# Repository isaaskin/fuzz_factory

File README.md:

# fuzz_factory
Fuzz Factory Guitar Effect Pedal

Schematic and layout drawing on Eagle Cad Software.
Ready to print. 
Potentiometer, LED, DC jack input, Battery input, 3.5mm mono input-output jack and 3DPT switch connections are ready on the board.
Minimalistic cable design.

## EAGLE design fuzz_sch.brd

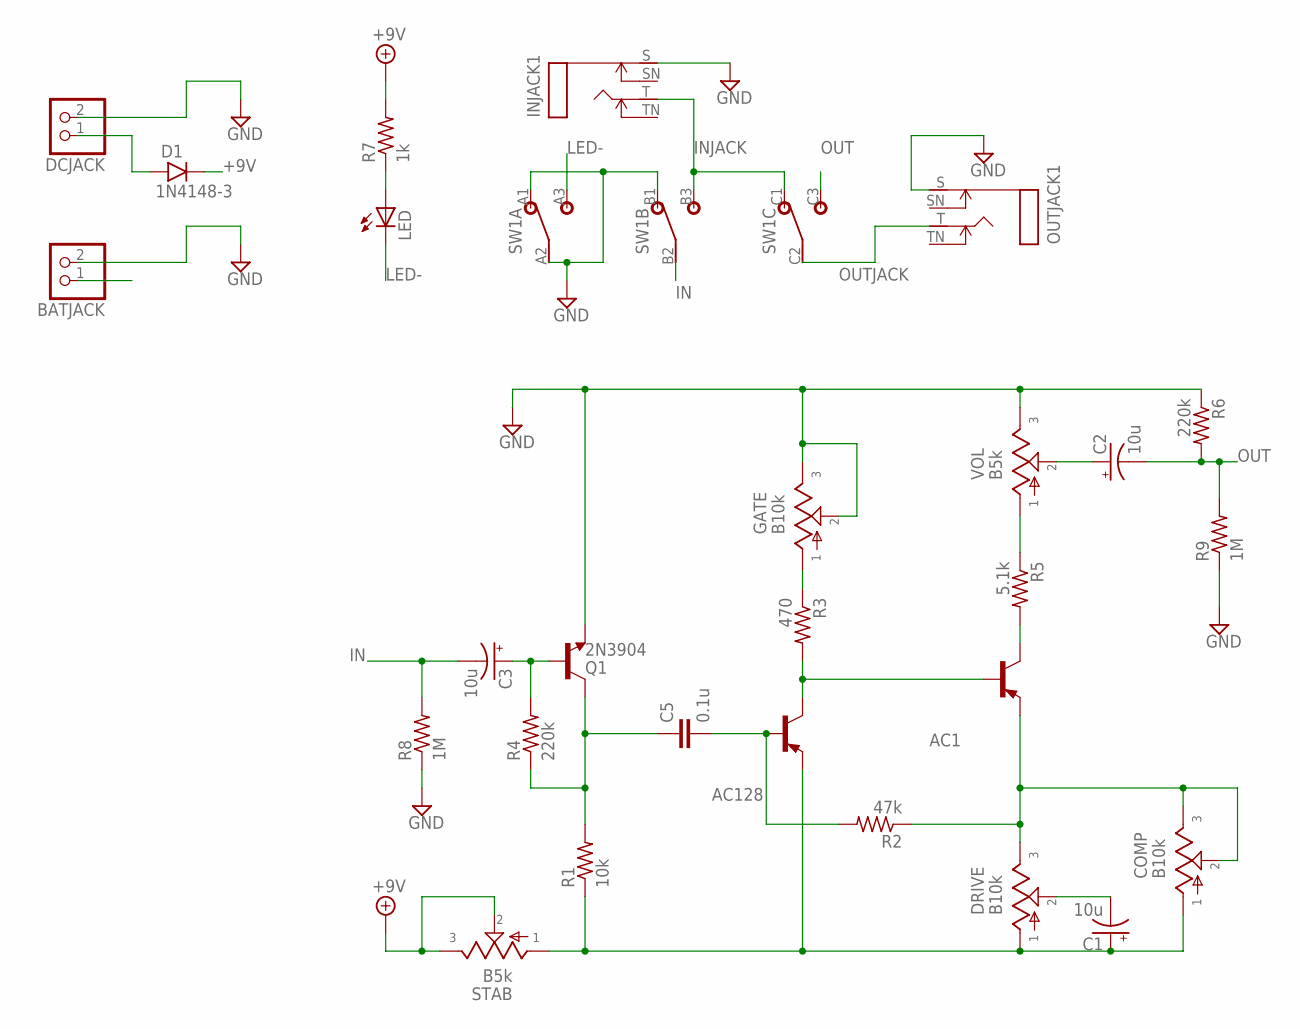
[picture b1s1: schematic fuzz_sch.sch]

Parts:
AC1, AC128: -PNP-TO5; TO5
BATJACK: PINHD-1X2; 1X02
C1, C2, C3: 10u; 063_025
C5: 0.1u; 072X035
COMP: B10k; 16MM
D1: 1N4148-3; DO35-3
DCJACK: PINHD-1X2; 1X02
DRIVE: B10k; 16MM
GATE: B10k; 16MM
INJACK1: MONOSWS; NMJ4HC-S
LED: LED5MM
OUTJACK1: MONOSWS; NMJ4HC-S
Q1: 2N3904; TO92-
R1: 10k; 0207/10
R2: 47k; 0207/10
R3: 470; 0207/10
R4, R6: 220k; 0207/10
R5: 5.1k; 0207/10
R7: 1k; 0207/10
R8, R9: 1M; 0207/10
STAB: B5k; 16MM
SW1: 3PDTBLUE; CHINABLUE
VOL: B5k; 16MM

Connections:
+9V: BATJACK.1, D1.C, R7.2, STAB.2, STAB.3
GND: BATJACK.2, DCJACK.2, GATE.2, GATE.3, INJACK1.S, OUTJACK1.S, Q1.3 (E), R6.1, R8.1, R9.1, SW1.A1 (1), SW1.A2 (2), SW1.B1 (1), VOL.3
IN: C3.-, R8.2, SW1.B2 (2)
INJACK: INJACK1.T, SW1.B3 (3), SW1.C1 (1)
LED-: LED.K (C), SW1.A3 (3)
unnamed: C3.+, Q1.2 (B), R4.2
unnamed: C5.1, Q1.1 (C), R1.2, R4.1
unnamed: AC128.1 (E), C1.+, COMP.1, DRIVE.1, R1.1, STAB.1
unnamed: AC128.2 (B), C5.2, R2.2
unnamed: C2.+, VOL.2
unnamed: AC1.2 (B), AC128.3 (C), R3.2
unnamed: GATE.1, R3.1
unnamed: LED.A, R7.1
unnamed: D1.A, DCJACK.1
unnamed: C1.-, DRIVE.2
unnamed: AC1.1 (E), COMP.2, COMP.3, DRIVE.3, R2.1
unnamed: R5.1, VOL.1
unnamed: AC1.3 (C), R5.2
OUT: C2.-, R6.2, R9.2, SW1.C3 (3)
OUTJACK: OUTJACK1.T, SW1.C2 (2)

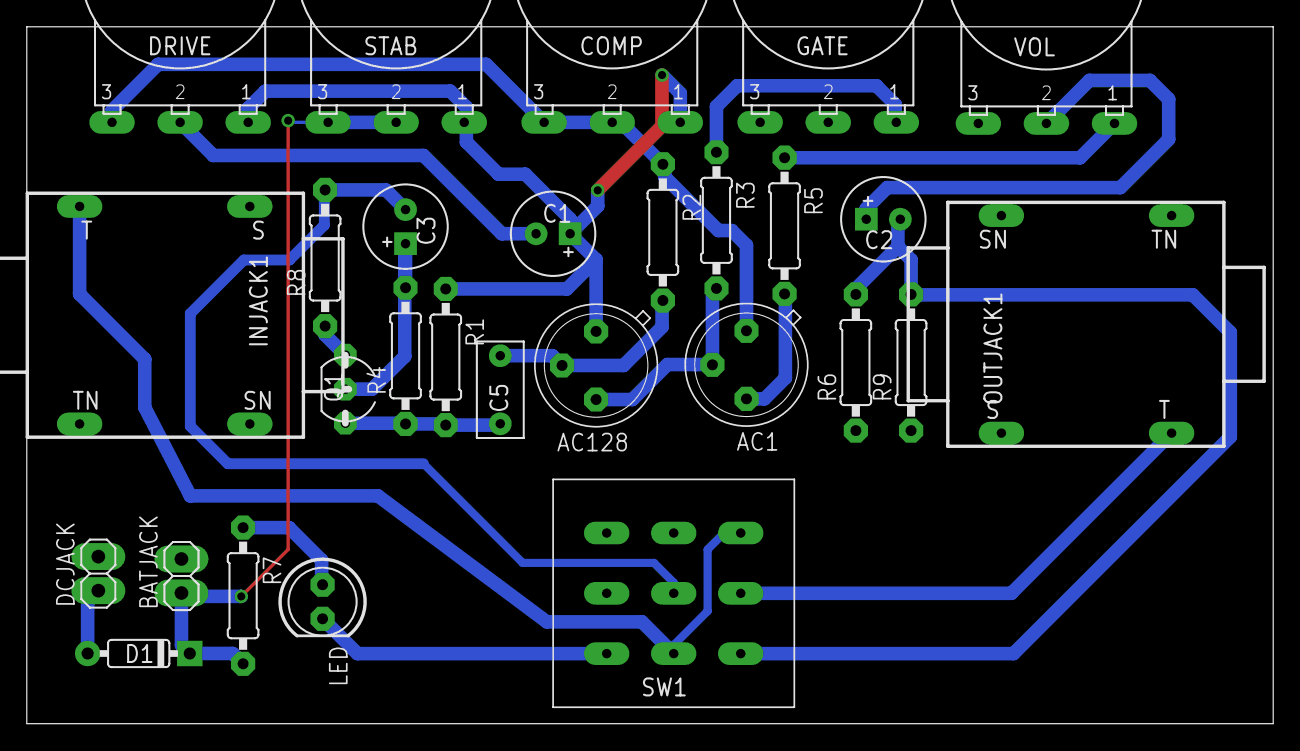
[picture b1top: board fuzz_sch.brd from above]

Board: 2 copper layers, 93.0 x 52.0 mm, 28 parts (0 on the bottom side), 20 nets.

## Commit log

2017-04-28 Fuzz Factory
    Fuzz factory guitar pedal's schematic and layout drawing by Eagle Cad
    Software.
